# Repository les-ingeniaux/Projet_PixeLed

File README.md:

# Projet PixeLed

Vous trouverez dans le dossier code les fichiers à utiliser pour personnaliser votre PixeLed.
Vous pouvez les télécharger et les transférer sur votre Raspberry Pi Pico W en utilisant Thonny: une fois cela fait, vous pourrez librement éditer le fichier main.py pour y ajouter votre code.

Bon courage !

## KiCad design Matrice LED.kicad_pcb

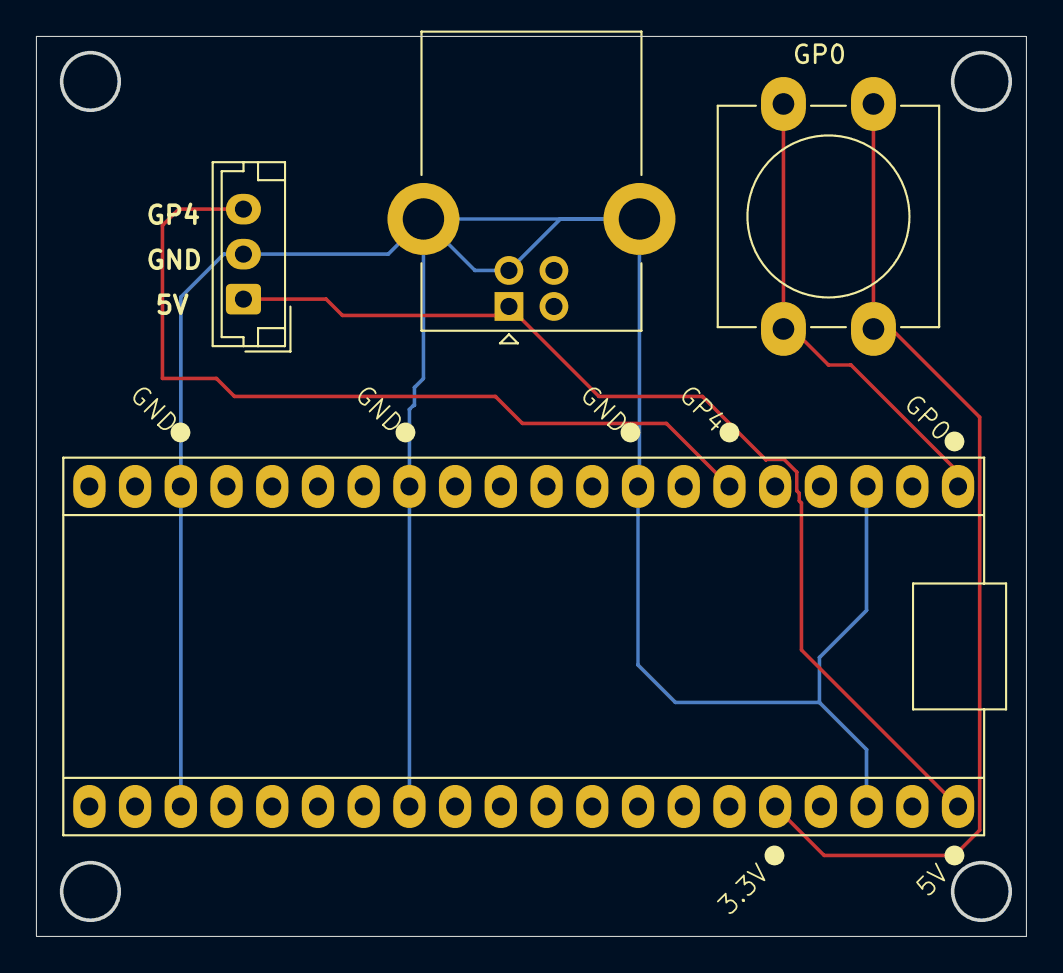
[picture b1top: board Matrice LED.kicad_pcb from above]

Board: 2 copper layers, 54.9 x 49.9 mm, 4 parts (0 on the bottom side), 5 nets.

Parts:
A1: RaspberryPi_Pico_W; raspberry_pi_pico_THT
GP0: Push_Button_W12mm
J1: Conn_01x03_Socket; JST_EH_B3B-EH-A_1x03_P2.50mm_Vertical
J2: USB_B; USB_B_Lumberg_2411_02_Horizontal

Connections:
+5V: A1.40 (VBUS), J1.1, J2.1 (VBUS)
/GP4: A1.6 (GPIO4), J1.3
GND: A1.3 (GND), A1.8 (GND), A1.13 (GND), A1.18 (GND), A1.23 (GND), A1.28 (GND), A1.38 (GND), J1.2, J2.4 (GND), J2.5 (Shield)
unnamed: A1.36 (3V3), GP0.1
unnamed: A1.1 (GPIO0), GP0.2

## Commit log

2026-02-02 Ajout du boitier
2026-02-02 Kicad
2026-02-05 Juste pour voir
2026-02-05 Fix #1
2026-02-06 Code Micropython
2026-03-24 New layout
2026-03-26 Final version
    As ordered from PCBWay on 26/03/2026
2026-03-27 Clean-up
    Cleaned up the folder by moving files to dedicated folders
    Added the latest 3D export of the PCB as step
2026-04-23 Complete rewrite
    - Code is now subdivided into different files
    - All the network and wifi features are now properly organized in their dedicated file that the students should not need to change unless they want to
    - exampleAnimations and exampleImages are the two files that should be used as main.py depending on whether the student has chosen to use animations or images
    - utilitairesLed introduces a number of utility features (some of which might be removed in the future so the students can create them from scratch)
    - the state file allows the webserver to change the value of global variables that are then used in the main loop
    - the html page has been totally revamped to allow for a nice ex
2026-05-18 Added new branch
    Added new branch to keep complete code in order to keep only the right files on the main branch
2026-05-18 Main branch can now be given to students
    Removed a few files from the main branch so that the students start from a clean slate
    Added some docstrings to the utilities functions to provide guidance on how to use them
2026-05-18 Added a Readme
2026-06-03 main.py now consistent with documentation
    Updated main.py to be consistent with the pseudo code given in the project docs : now checking if state.allumage==0 rather than 1
2026-06-03 Typo fix
2026-06-17 Added CSS style from Selena
2026-06-17 Added Andre's version of the server with the functionning color picker
2026-06-17 Added Andre's state file
2026-06-17 Added Selena's page
